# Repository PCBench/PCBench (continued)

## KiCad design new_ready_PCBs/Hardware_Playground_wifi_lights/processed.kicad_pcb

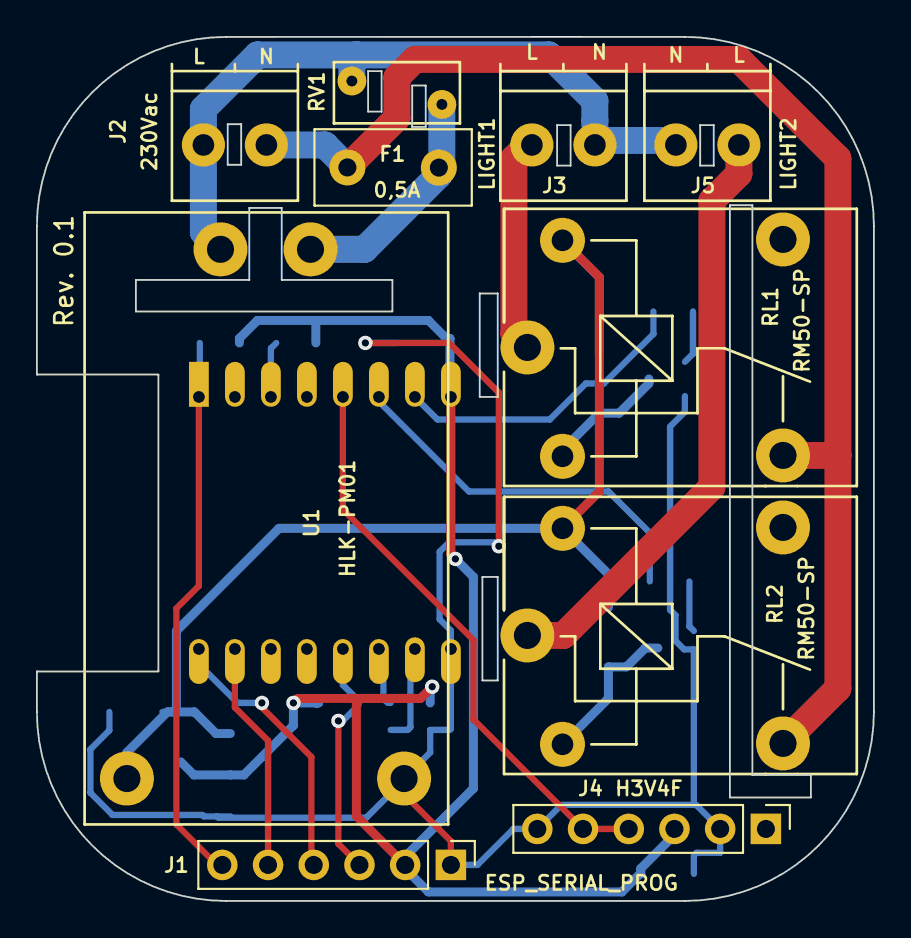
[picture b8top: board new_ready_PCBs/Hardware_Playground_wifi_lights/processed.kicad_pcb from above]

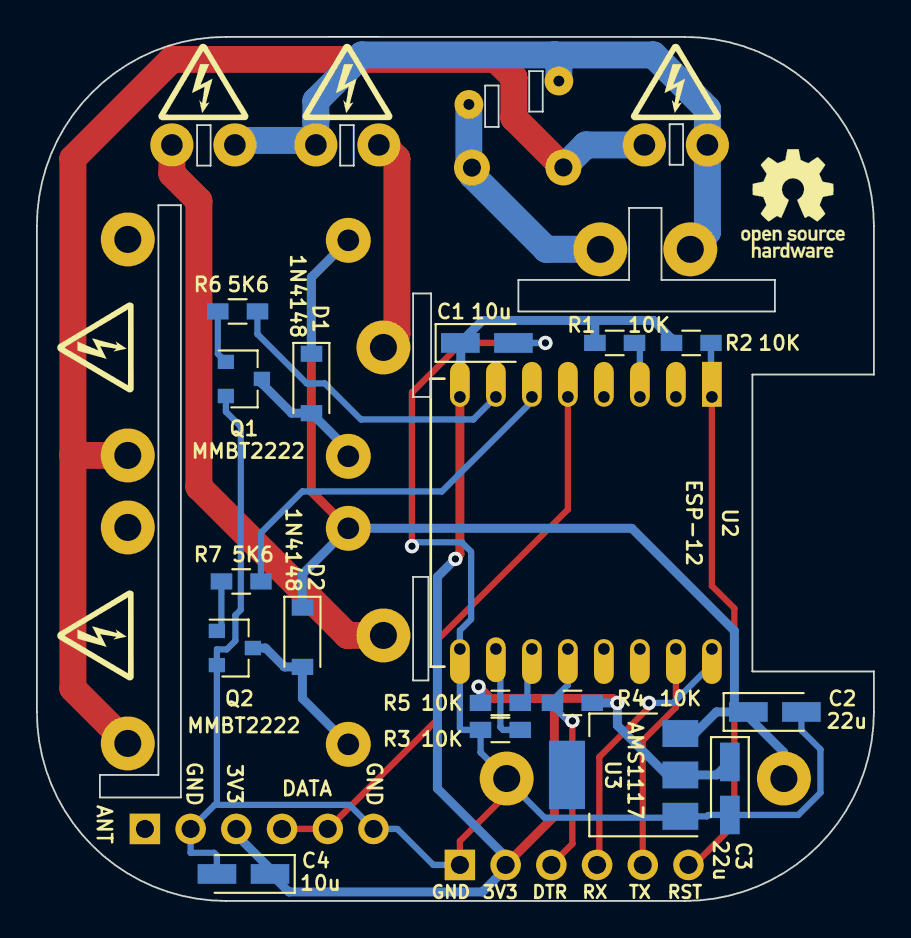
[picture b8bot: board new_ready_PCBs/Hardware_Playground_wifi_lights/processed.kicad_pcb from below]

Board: 2 copper layers, 46.5 x 48.0 mm, 27 parts (17 on the bottom side), 22 nets.

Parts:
C1, C4: 10u; CP_Tantalum_Case-A_EIA-3216-18_Wave
C2, C3: 22u; CP_Tantalum_Case-A_EIA-3216-18_Wave
D1, D2: 1N4148; D_SOD-123
F1: 0,5A; Fuse_TE5_Littlefuse-395Series
J1: ESP_SERIAL_PROG; Pin_Header_Straight_1x06_Pitch2.54mm
J2: 230Vac; TerminalBlock_Pheonix_PT-3.5mm_2pol
J3: LIGHT1; TerminalBlock_Pheonix_PT-3.5mm_2pol
J4: H3V4F; Pin_Header_Straight_1x06_Pitch2.54mm
J5: LIGHT2; TerminalBlock_Pheonix_PT-3.5mm_2pol
Q1, Q2: MMBT2222; SOT-23
R1, R2, R3, R4, R5: 10K; R_0603_HandSoldering
R6, R7: 5K6; R_0603_HandSoldering
RL1, RL2: RM50-SP; RM50_P
RV1: Varistor; RV_Disc_D7_W3.4_P5
U1: ESP-12
U2: HLK-PM01
U3: AMS1117; SOT-223

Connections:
+3V3: C1.1, C3.1, C4.1, J1.2, J4.3, R1.2, R2.2, R4.2, R5.2, U1.8, U3.2
+5V: C2.1, D1.1, D2.1, RL1.A1, RL2.A1, U2.3, U3.3
/433_RX_DATA: J4.4, J4.5, U1.5
/DTR: J1.3, R4.1, U1.12
/L: F1.1, J2.1, RL1.14, RL2.14
/N: J2.2, J3.1, J5.2, RV1.2, U2.2
/RELAY_CH1: R6.2, U1.7
/RELAY_CH2: R7.2, U1.6
/REL_SW1: J3.2, RL1.11
/REL_SW2: J5.1, RL2.11
/RESET: J1.6, R2.1, U1.1
/RX: J1.4, U1.16
/TX: J1.5, U1.15
GND: C1.2, C2.2, C3.2, C4.2, J1.1, J4.2, J4.6, Q1.2, Q2.2, R3.1, U1.9, U2.4, U3.1
unnamed: D1.2, Q1.3, RL1.A2
unnamed: D2.2, Q2.3, RL2.A2
unnamed: F1.2, RV1.1, U2.1
unnamed: Q1.1, R6.1
unnamed: Q2.1, R7.1
unnamed: R1.1, U1.3
unnamed: R3.2, U1.10
unnamed: R5.1, U1.11
